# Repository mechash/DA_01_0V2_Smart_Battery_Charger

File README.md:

# DA_01_0V2_Smart_Battery_Charger
 Freelance Project

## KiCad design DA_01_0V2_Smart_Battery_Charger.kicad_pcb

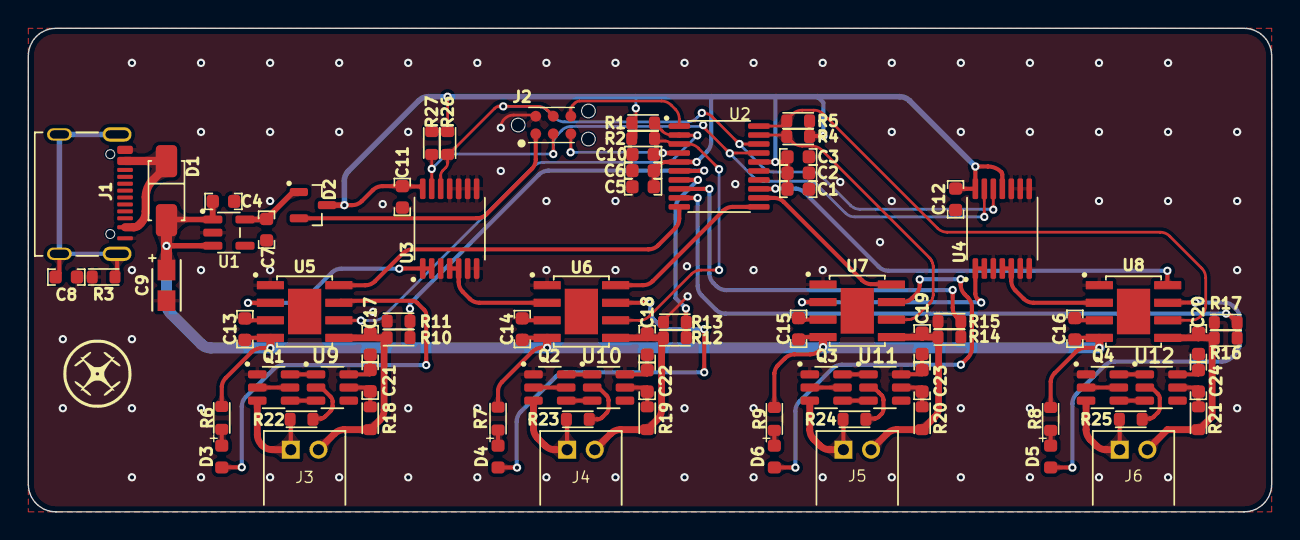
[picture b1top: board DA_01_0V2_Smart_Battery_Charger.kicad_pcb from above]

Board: 2 copper layers, 90.0 x 35.0 mm, 79 parts (0 on the bottom side), 59 nets.

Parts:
C1: 4.7uf; C_0603
C2, C3, C8, C10, C11, C12, C21, C22, C23, C24: 100nf; C_0603
C4, C5, C7: 1uf; C_0603
C6: 10nf; C_0603
C9: 10uf; C_E_1206
C13, C14, C15, C16, C17, C18, C19, C20: 10uf; C_0603
D1: SS34; DO-214
D2: RB495D; SOT-23-3
D3, D4, D5, D6: R/G/B; LED_0603
J1: USB_C_12402012E212A
J2: TC2030-IDC-NL; TAG_TC2030-IDC-NL
J3, J4, J5, J6: JST_S2B-PH-K-S(LF)(SN)
Q1, Q2, Q3, Q4: DMG6968UDM-7; SOT-23-6
R1, R2, R4, R5, R6, R7, R8, R9: 1k; R_0603
R3, R18, R19, R20, R21: 330R; R_0603
R10, R12, R14, R16: 4.7k; R_0603
R11, R13, R15, R17: 15k; R_0603
R22, R23, R24, R25, R26, R27: 2k7; R_0603
U1: MIC5504-3.3YM5-TR; SOT-23-5
U2: STM32F030F4P6; TSSOP-20
U3, U4: MAX5387LAUDT+; TSSOP-14
U5, U6, U7, U8: TP4056; SOP8-EP
U9, U10, U11, U12: AP9101CAK6-ATTRG1; SOT-23-6

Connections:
+3.3V: C1.1, C2.1, C3.1, C5.1, C6.1, C11.1, C12.1, D2.3, R1.1, R2.1, R4.1, R5.1, R26.2, R27.2, U2.5 (VDDA), U2.16 (VDD), U3.14 (VDD), U4.11 (A0), U4.14 (VDD)
+BAT_1: C17.1, J3.2, R10.1, R18.1, U5.5 (BAT)
+BAT_2: C18.1, J4.2, R12.1, R19.1, U6.5 (BAT)
+BAT_3: C19.1, J5.2, R14.1, R20.1, U7.5 (BAT)
+BAT_4: C20.1, J6.2, R16.1, R21.1, U8.5 (BAT)
/+3.3_PROG: D2.2, J2.1
/BAT_1_CE: U2.10 (PA4), U5.8 (CE)
/BAT_1_CHRG: D3.1 (K), U5.7 (~CHRG)
/BAT_1_PROG: U3.1 (HA), U3.2 (WA), U5.2 (PROG)
/BAT_1_STDBY: R1.2, U2.2 (PF0/OSC_IN), U5.6 (~STDBY)
/BAT_1_V: R10.2, R11.2, U2.6 (PA0)
/BAT_2_CE: U2.11 (PA5), U6.8 (CE)
/BAT_2_CHRG: D4.1 (K), U6.7 (~CHRG)
/BAT_2_PROG: U3.4 (HB), U3.5 (WB), U6.2 (PROG)
/BAT_2_STDBY: R2.2, U2.3 (PF1/OSC_OUT), U6.6 (~STDBY)
/BAT_2_V: R12.2, R13.2, U2.7 (PA1)
/BAT_3_CE: U2.12 (PA6), U7.8 (CE)
/BAT_3_CHRG: D6.1 (K), U7.7 (~CHRG)
/BAT_3_PROG: U4.1 (HA), U4.2 (WA), U7.2 (PROG)
/BAT_3_STDBY: R4.2, U2.19 (PA13), U7.6 (~STDBY)
/BAT_3_V: R14.2, R15.2, U2.8 (PA2)
/BAT_4_CE: U2.13 (PA7), U8.8 (CE)
/BAT_4_CHRG: D5.1 (K), U8.7 (~CHRG)
/BAT_4_PROG: U4.4 (HB), U4.5 (WB), U8.2 (PROG)
/BAT_4_STDBY: R5.2, U2.20 (PA14), U8.6 (~STDBY)
/BAT_4_V: R16.2, R17.2, U2.9 (PA3)
/BOOT0: J2.6, U2.1 (BOOT0)
/NRST: C10.2, J2.5, U2.4 (NRST)
/SCL_TX: J2.3, R27.1, U2.17 (PA9), U3.13 (SCL), U4.13 (SCL)
/SDA_RX: J2.4, R26.1, U2.18 (PA10), U3.12 (SDA), U4.12 (SDA)
GND: C1.2, C2.2, C3.2, C4.2, C5.2, C6.2, C7.2, C8.2, C9.1, C10.1, C11.2, C12.2, C13.2, C14.2, C15.2, C16.2, C17.2, C18.2, C19.2, C20.2, C21.1, C22.1, C23.1, C24.1, J1.A1_B12 (GND), J1.B1_A12 (GND), J2.2, Q1.1 (S1), Q2.1 (S1), Q3.1 (S1), Q4.1 (S1), R3.2, R11.1, R13.1, R15.1, R17.1, U1.2 (GND), U2.15 (VSS), U3.3 (LA), U3.6 (LB), U3.7 (I.C.), U3.8 (GND), U3.9 (A2), U3.10 (A1), U3.11 (A0), U4.3 (LA), U4.6 (LB), U4.7 (I.C.), U4.8 (GND), U4.9 (A2), U4.10 (A1), U5.1 (TEMP), U5.3 (GND), U6.1 (TEMP), U6.3 (GND), U7.1 (TEMP), U7.3 (GND), U8.1 (TEMP), U8.3 (GND), U9.6 (VSS), U10.6 (VSS), U11.6 (VSS), U12.6 (VSS)
unnamed: C8.1, J1.SH1 (SHIELD), J1.SH2 (SHIELD), J1.SH3 (SHIELD), J1.SH4 (SHIELD), R3.1
unnamed: D1.2 (A), J1.A4_B9 (VBUS), J1.B4_A9 (VBUS)
unnamed: D3.2 (A), R6.2
unnamed: D4.2 (A), R7.2
unnamed: D5.2 (A), R8.2
unnamed: D6.2 (A), R9.2
unnamed: Q1.6 (G1), U9.1 (DO)
unnamed: Q1.4 (G2), U9.3 (CO)
unnamed: J3.1, Q1.3 (S2), R22.2
unnamed: Q2.6 (G1), U10.1 (DO)
unnamed: Q2.4 (G2), U10.3 (CO)
unnamed: J4.1, Q2.3 (S2), R23.2
unnamed: Q3.6 (G1), U11.1 (DO)
unnamed: Q3.4 (G2), U11.3 (CO)
unnamed: J5.1, Q3.3 (S2), R24.2
unnamed: Q4.6 (G1), U12.1 (DO)
unnamed: Q4.4 (G2), U12.3 (CO)
unnamed: J6.1, Q4.3 (S2), R25.2
unnamed: C7.1, D2.1, U1.5 (VOUT)
unnamed: C21.2, R18.2, U9.5 (VDD)
unnamed: R22.1, U9.2 (VM)
unnamed: C22.2, R19.2, U10.5 (VDD)
unnamed: R23.1, U10.2 (VM)
unnamed: C23.2, R20.2, U11.5 (VDD)
unnamed: R24.1, U11.2 (VM)
unnamed: C24.2, R21.2, U12.5 (VDD)
unnamed: R25.1, U12.2 (VM)
VBUS: C4.1, C9.2, C13.1, C14.1, C15.1, C16.1, D1.1 (K), R6.1, R7.1, R8.1, R9.1, U1.1 (VIN), U1.3 (EN), U5.4 (VCC), U6.4 (VCC), U7.4 (VCC), U8.4 (VCC)

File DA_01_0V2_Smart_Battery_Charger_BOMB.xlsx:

Source: | F:\KiCad\DA_01_0V2_Smart_Battery_Charger\DA_01_0V2_Smart_Battery_Charger.kicad_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
Date: | 45090.828888888886
Tool: | Eeschema 7.0.2
Generator: | C:\Program Files\KiCad\7.0\bin\scripting\plugins/bom_csv_grouped_by_value.py
Component Count: | 77
Collated Components:
Item | Qty | Reference(s) | Comment | LibPart | Footprint |  |  |  | LCSC | MANUFACTURER
1 | 1 | C1 | 4.7uf | MechAsh_Library:C_0402 | MechAsh_Footprint_Library:C_0402
2 | 10 | C2, C3, C8, C10, C11, C12, C21, C22, C23, C24 | 100nf | MechAsh_Library:C_0402 | MechAsh_Footprint_Library:C_0402
3 | 3 | C4, C5, C7 | 1uf | MechAsh_Library:C_0402 | MechAsh_Footprint_Library:C_0402
4 | 1 | C6 | 10nf | MechAsh_Library:C_0402 | MechAsh_Footprint_Library:C_0402
5 | 1 | C9 | 10uf | MechAsh_Library:C_E_1206_T | MechAsh_Footprint_Library:C_E_1206
6 | 8 | C13, C14, C15, C16, C17, C18, C19, C20 | 10uf | MechAsh_Library:C_0402 | MechAsh_Footprint_Library:C_0402
7 | 1 | D1 | SS34 | MechAsh_Library:SD_DO_14 | MechAsh_Footprint_Library:DO-214 |  |  |  | C8678
8 | 1 | D2 | RB495D | MechAsh_Library:SD_SOT23_3 | MechAsh_Footprint_Library:SOT-23-3
9 | 4 | D3, D4, D5, D6 | R/G/B | MechAsh_Library:LED_0603 | MechAsh_Footprint_Library:LED_0603
10 | 1 | J1 | USB_C_12402012E212A | MechAsh_Library:USB_C_12402012E212A | MechAsh_Footprint_Library:USB_C_12402012E212A
11 | 1 | J2 | TC2030-IDC-NL | MechAsh_Library:TC2030-IDC-NL | MechAsh_Footprint_Library:TAG_TC2030-IDC-NL
12 | 4 | J3, J4, J5, J6 | JST_S2B-PH-K-S(LF)(SN) | MechAsh_Library:JST_S2B-PH-K-S(LF)(SN) | MechAsh_Footprint_Library:JST_S2B-PH-K-S(LF)(SN)
13 | 4 | Q1, Q2, Q3, Q4 | DMG6968UDM-7 | MechAsh_Library:DMG6968UDM-7 | MechAsh_Footprint_Library:SOT-23-6
14 | 8 | R1, R2, R4, R5, R6, R7, R8, R9 | 1k | MechAsh_Library:R_0402 | MechAsh_Footprint_Library:R_0402
15 | 5 | R3, R18, R19, R20, R21 | 330R | MechAsh_Library:R_0402 | MechAsh_Footprint_Library:R_0402
16 | 4 | R10, R12, R14, R16 | 4.7k | MechAsh_Library:R_0402 | MechAsh_Footprint_Library:R_0402
17 | 4 | R11, R13, R15, R17 | 15k | MechAsh_Library:R_0402 | MechAsh_Footprint_Library:R_0402
18 | 4 | R22, R23, R24, R25 | 2k7 | MechAsh_Library:R_0402 | MechAsh_Footprint_Library:R_0402
19 | 1 | U1 | MIC5504-3.3YM5-TR | MechAsh_Library:MIC5504-3.3YM5_TR | MechAsh_Footprint_Library:SOT-23-5 |  |  |  |  | Microchip
20 | 1 | U2 | STM32F030F4P6 | MechAsh_Library:STM32F030F4P6 | MechAsh_Footprint_Library:TSSOP-20
21 | 2 | U3, U4 | MAX5387LAUDT+ | MechAsh_Library:MAX5387LAUDT | MechAsh_Footprint_Library:TSSOP-14
22 | 4 | U5, U6, U7, U8 | TP4056 | MechAsh_Library:TP4056 | MechAsh_Footprint_Library:SOP8-EP
23 | 4 | U9, U10, U11, U12 | AP9101CK-AHTRG1 | MechAsh_Library:AP9101CK-AHTRG1 | MechAsh_Footprint_Library:SOT-753-5 |  |  |  |  | Diodes Incorporated
